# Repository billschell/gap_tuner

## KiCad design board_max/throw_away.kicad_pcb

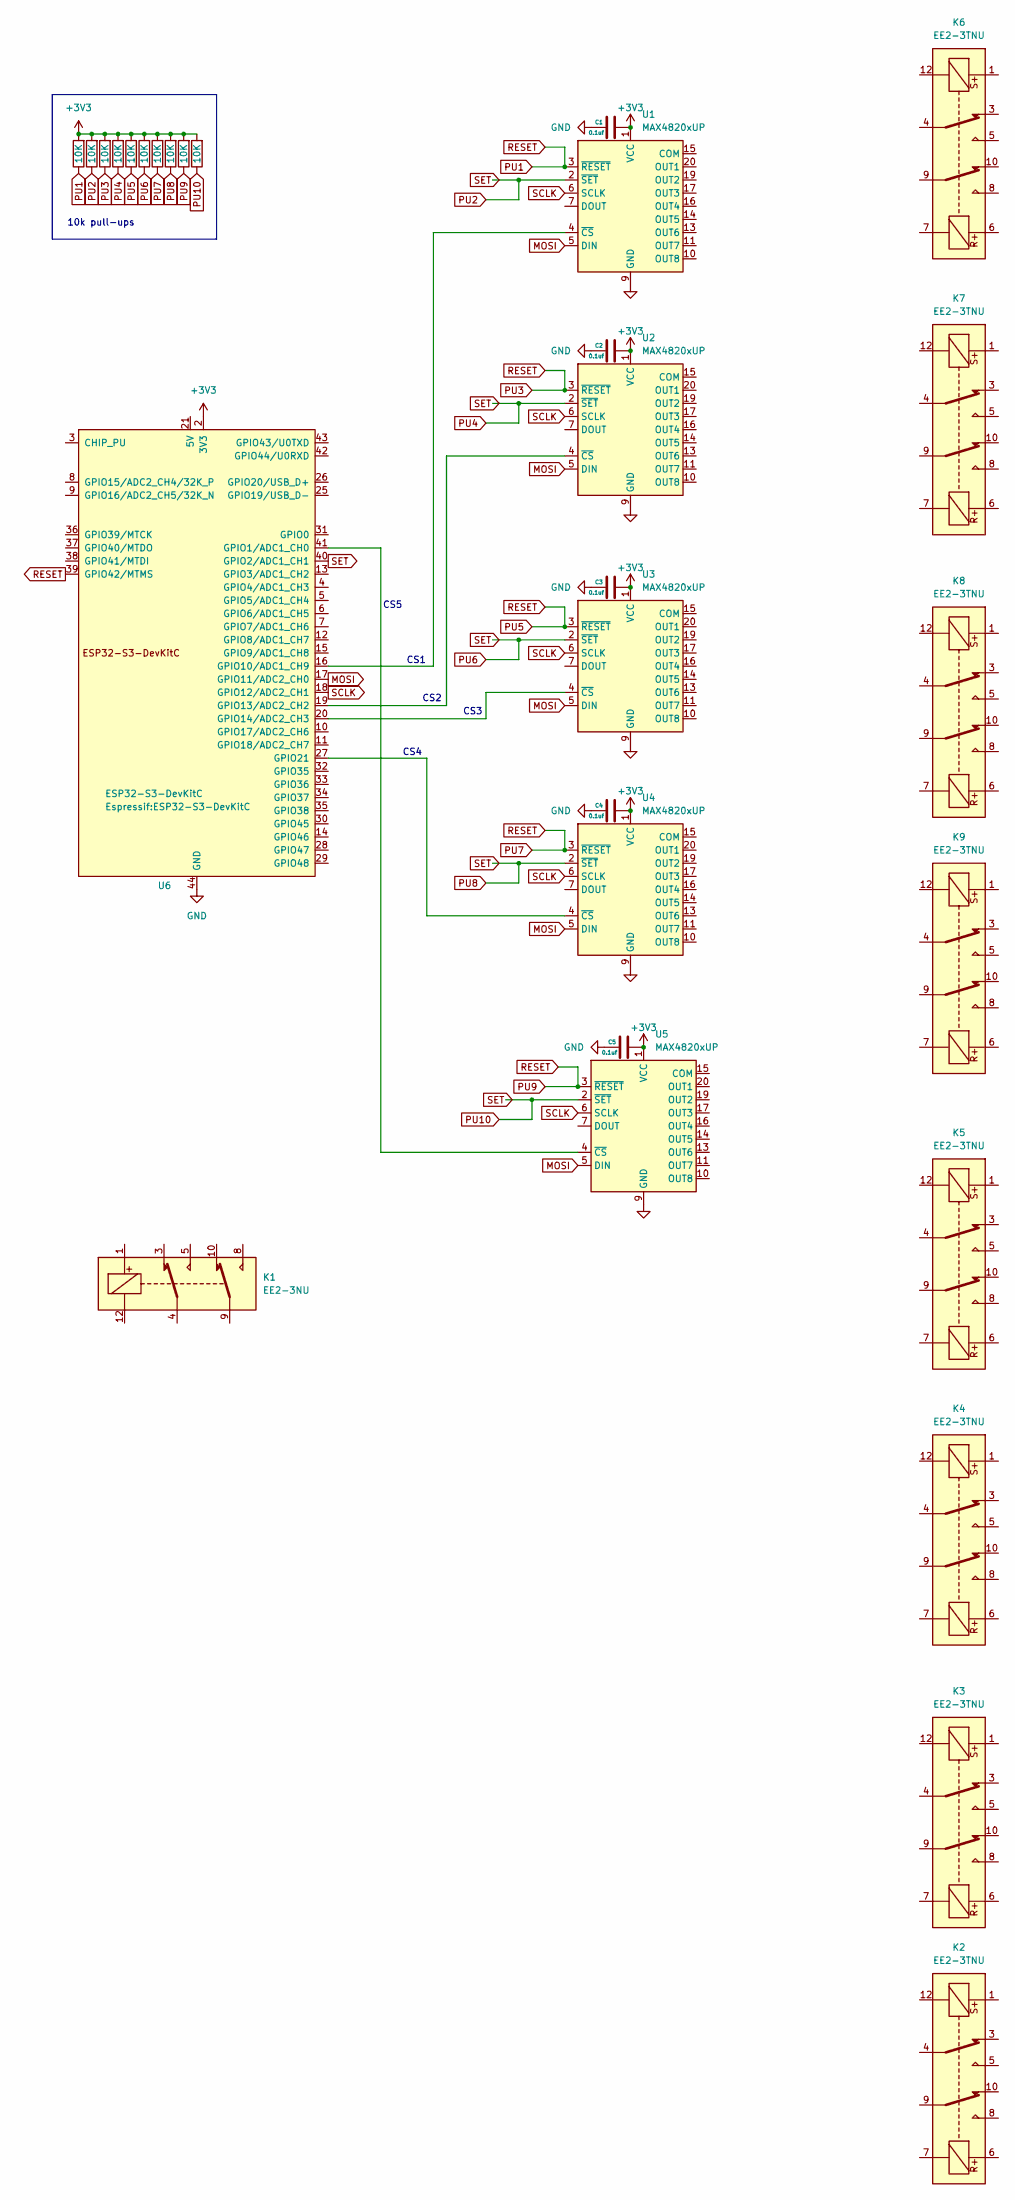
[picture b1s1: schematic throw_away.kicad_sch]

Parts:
C1, C2, C3, C4, C5: 0.1uf; C_0805_2012Metric_Pad1.18x1.45mm_HandSolder
K1: EE2-3NU; Relay_DPDT_Kemet_EE2_NU
K2, K3, K4, K5, K6, K7, K8, K9: EE2-3TNU; Relay_DPDT_Kemet_EE2_NU_DoubleCoil
R11, R12, R13, R14, R15, R16, R17, R18, R19, R20: 10K; R_0805_2012Metric_Pad1.20x1.40mm_HandSolder
U1, U2, U3, U4, U5: MAX4820xUP; HTSSOP-20-1EP_4.4x6.5mm_P0.65mm_EP2.85x4mm
U6: ESP32-S3-DevKitC

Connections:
+3V3: C1.2, C2.2, C3.2, C4.2, C5.2, R11.2, R12.2, R13.2, R14.2, R15.2, R16.2, R17.2, R18.2, R19.2, R20.2, U1.1 (VCC), U2.1 (VCC), U3.1 (VCC), U4.1 (VCC), U5.1 (VCC), U6.1 (3V3), U6.2 (3V3)
GND: C1.1, C2.1, C3.1, C4.1, C5.1, U1.9 (GND), U1.12 (GND), U1.18 (GND), U1.21 (GND), U2.9 (GND), U2.12 (GND), U2.18 (GND), U2.21 (GND), U3.9 (GND), U3.12 (GND), U3.18 (GND), U3.21 (GND), U4.9 (GND), U4.12 (GND), U4.18 (GND), U4.21 (GND), U5.9 (GND), U5.12 (GND), U5.18 (GND), U5.21 (GND), U6.22 (GND), U6.23 (GND), U6.24 (GND), U6.44 (GND)
MOSI: U1.5 (DIN), U2.5 (DIN), U3.5 (DIN), U4.5 (DIN), U5.5 (DIN), U6.17 (GPIO11/ADC2_CH0)
unnamed: U1.4 (~CS), U6.16 (GPIO10/ADC1_CH9)
unnamed: U2.4 (~CS), U6.19 (GPIO13/ADC2_CH2)
unnamed: U3.4 (~CS), U6.20 (GPIO14/ADC2_CH3)
unnamed: U4.4 (~CS), U6.27 (GPIO21)
unnamed: U5.4 (~CS), U6.41 (GPIO1/ADC1_CH0)
PU1: R11.1, R13.1, R15.1, R17.1, R19.1, U1.3 (~RESET), U2.3 (~RESET), U3.3 (~RESET), U4.3 (~RESET), U5.3 (~RESET), U6.39 (GPIO42/MTMS)
PU10: R12.1, R14.1, R16.1, R18.1, R20.1, U1.2 (~SET), U2.2 (~SET), U3.2 (~SET), U4.2 (~SET), U5.2 (~SET), U6.40 (GPIO2/ADC1_CH1)
SCLK: U1.6 (SCLK), U2.6 (SCLK), U3.6 (SCLK), U4.6 (SCLK), U5.6 (SCLK), U6.18 (GPIO12/ADC2_CH1)

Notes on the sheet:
CS5
CS2
CS1
10k pull-ups
CS4
CS3

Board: 2 copper layers, 30 parts (0 on the bottom side), 11 nets, no tracks yet.

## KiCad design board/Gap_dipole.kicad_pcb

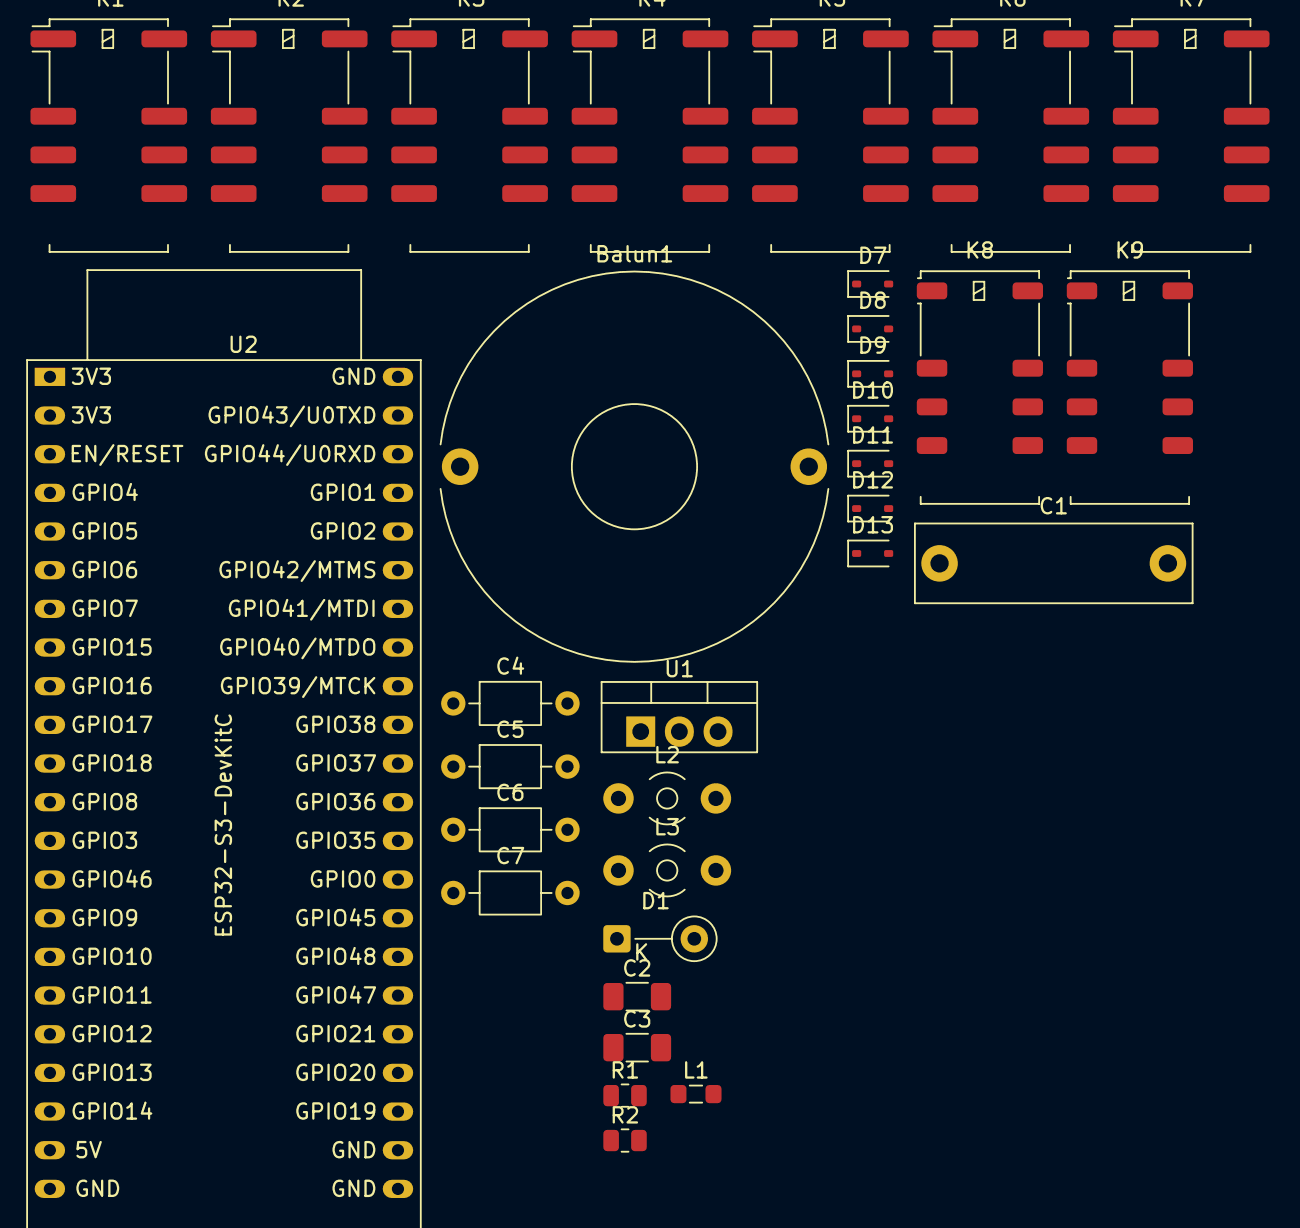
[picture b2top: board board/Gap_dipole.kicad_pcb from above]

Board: 2 copper layers, 32 parts (0 on the bottom side), 34 nets, no tracks yet.

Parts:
Balun1: toroidal core (fix connections); L_Toroid_Horizontal_D25.4mm_P22.90mm_Vishay_TJ5
C1: .47K100P (470 pF); C_Rect_L18.0mm_W5.0mm_P15.00mm_FKS3_FKP3
C2, C3: C; C_1206_3216Metric_Pad1.33x1.80mm_HandSolder
C4, C5, C6, C7: C; C_Axial_L3.8mm_D2.6mm_P7.50mm_Horizontal
D1: D; D_A-405_P5.08mm_Vertical_KathodeUp
D7, D8, D9, D10, D11, D12, D13: 1N4148WS; D_SOD-323
K1, K2, K3, K4, K5, K6, K7: EE2-3NU; Relay_DPDT_Kemet_EE2_NU
K8, K9: EE2-3SNUH; Relay_DPDT_Kemet_EE2_NUH
L1: L - bias tee; L_0805_2012Metric_Pad1.05x1.20mm_HandSolder
L2, L3: L; L_Toroid_Horizontal_D3.2mm_P6.40mm_Diameter3-5mm_Amidon-T12
R1, R2: 100Ω; R_0805_2012Metric
U1: REG; TO-220-3_Vertical
U2: ESP32-S3-DevKitC

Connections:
+3.3V: C1.2, K7.5, K7.10
GNDREF: Balun1.1 (AA), C2.2, C3.2, D7.2 (A), D8.2 (A), D9.2 (A), D10.2 (A), D11.2 (A), D12.2 (A), D13.2 (A), K1.12, K2.3, K2.10, K2.12, K3.12, K4.12, K5.12, K6.1, K7.3, K7.8, K7.12, R1.2, R2.2, U1.2 (GND)
unnamed: Balun1.2 (AB), K4.4
unnamed: K6.3, K6.10
unnamed: K5.3, K5.10
unnamed: C1.1, K1.4, K1.9, L1.1
unnamed: C4.1, K8.8
unnamed: C4.2, K8.5
unnamed: C5.1, K8.1, K8.9, L2.1
unnamed: C5.2, K8.4, K8.12, L2.2
unnamed: C6.1, K9.8
unnamed: C6.2, K9.5
unnamed: C7.1, K9.1, K9.9, L3.1
unnamed: C7.2, K9.4, K9.12, L3.2
unnamed: D1.2 (A), L1.2
unnamed: C2.1, D1.1 (K), U1.1 (VI)
unnamed: D7.1 (K), K1.1
unnamed: D8.1 (K), K2.1
unnamed: D9.1 (K), K4.1
unnamed: D10.1 (K), K3.1
unnamed: D11.1 (K), K5.1
unnamed: D12.1 (K), K7.1
unnamed: D13.1 (K), K6.12
unnamed: K1.5, K1.8, K3.4, K3.9
unnamed: K1.3, K1.10, K2.4, K2.9
unnamed: K3.3, R2.1
unnamed: K3.5, K3.8, K4.9
unnamed: K3.10, R1.1
unnamed: K4.3, K4.10
unnamed: K5.5, K6.5, K7.4
unnamed: K5.8, K6.8, K7.9
unnamed: U2.1 (3V3), U2.2 (3V3)
unnamed: U2.22 (GND), U2.23 (GND), U2.24 (GND), U2.44 (GND)
VDC: C3.1, U1.3 (VO)

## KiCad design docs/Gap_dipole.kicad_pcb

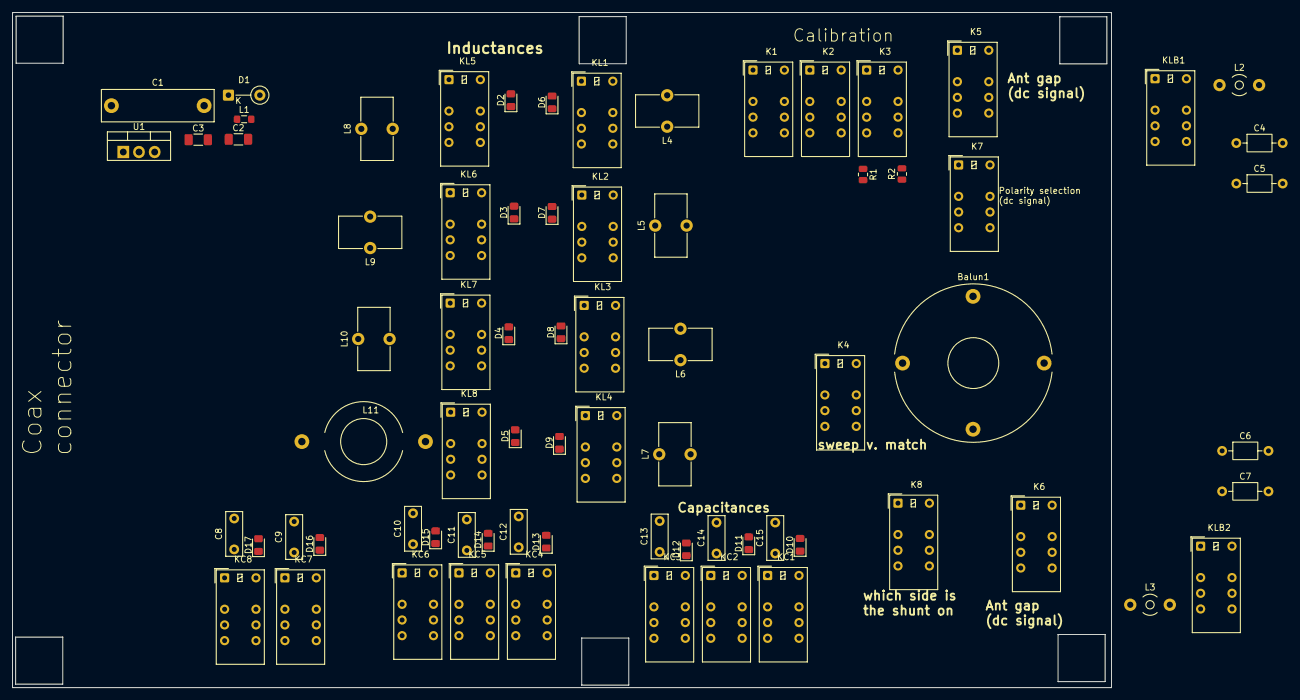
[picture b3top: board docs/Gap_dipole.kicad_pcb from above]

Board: 2 copper layers, 177.8 x 109.2 mm, 73 parts (0 on the bottom side), 21 nets, no tracks yet.

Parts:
Balun1: toroidal core (fix connections); L_Toroid_Horizontal_D25.4mm_P22.90mm_Vishay_TJ5
C1: .47K100P (470 pF); C_Rect_L18.0mm_W5.0mm_P15.00mm_FKS3_FKP3
C2, C3: C; C_1206_3216Metric_Pad1.33x1.80mm_HandSolder
C4, C5, C6, C7: C; C_Axial_L3.8mm_D2.6mm_P7.50mm_Horizontal
C8, C9, C10, C11, C12, C13, C14, C15: C; C_Disc_D7.0mm_W2.5mm_P5.00mm
D1: D; D_A-405_P5.08mm_Vertical_KathodeUp
D2, D3, D4, D5, D6, D7, D8, D9, D10, D11, D12, D13, D14, D15, D16, D17: D; D_0805_2012Metric_Pad1.15x1.40mm_HandSolder
K1, K2, K3, K5, K6, K7: Nonlatching; Relay_DPDT_Kemet_EC2_NU
K4: Nonlatching, sweep (energized) or match (unenergi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; Relay_DPDT_Kemet_EC2_NU
K8: Relay_DPDT_Latching_1coil (bipolar) sets shunt si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; Relay_DPDT_Kemet_EC2_NJ
KC1, KC2, KC3, KC4, KC5, KC6, KC7, KC8: Relay_DPDT_Latching_1coil (bipolar); Relay_DPDT_Kemet_EC2_NJ
KL1, KL2, KL3, KL4, KL5, KL6, KL7, KL8: Relay_DPDT_Latching_1coil (bipolar); Relay_DPDT_Kemet_EC2_NJ
KLB1, KLB2: Relay_DPDT_Latching_1coil (bipolar); Relay_DPDT_Kemet_EC2_NJ
L1: L - bias tee; L_0805_2012Metric_Pad1.05x1.20mm_HandSolder
L2, L3: L; L_Toroid_Horizontal_D3.2mm_P6.40mm_Diameter3-5mm_Amidon-T12
L4, L5, L6, L7, L8, L9, L10: L; L_Toroid_Vertical_L10.0mm_W5.0mm_P5.08mm
L11: L; L_Toroid_Horizontal_D12.7mm_P20.00mm_Diameter14-5mm_Amidon-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
R1, R2: 100Ω; R_0805_2012Metric
U1: REG; TO-220-3_Vertical

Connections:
+3.3V: C1.2, K7.5, K7.10
GNDREF: Balun1.1 (AA), C2.2, C3.2, K1.12, K2.5, K2.8, K2.12, K3.12, K4.12, K5.12, K6.1, K7.3, K7.8, R1.2, R2.2, U1.2 (GND)
unnamed: Balun1.2 (AB), K4.9
unnamed: Balun1.3 (SA), K6.3, K6.10
unnamed: Balun1.4 (SB), K5.3, K5.10
unnamed: C1.1, K1.4, K1.9, L1.1
unnamed: C5.1, L2.1
unnamed: C5.2, L2.2
unnamed: C7.1, L3.1
unnamed: C7.2, L3.2
unnamed: D1.2 (A), L1.2
unnamed: C2.1, D1.1 (K), U1.1 (VI)
unnamed: K1.5, K1.8, K2.4, K2.9
unnamed: K1.3, K1.10, K3.4, K3.9
unnamed: K3.5, R1.1
unnamed: K3.8, R2.1
unnamed: K3.3, K3.10, K4.4
unnamed: K4.5, K4.8
unnamed: K5.5, K6.5, K7.4
unnamed: K5.8, K6.8, K7.9
VDC: C3.1, U1.3 (VO)

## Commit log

2025-10-27 updates after Bob's review
2025-10-27 updated k3 to connect to LC when unenergized
2025-12-05 All components now on board
    Draft with all components on the board. However everything is basically a placeholder. Need actual device footprints, inc lead spacings, etc.
2025-12-13 replaced generic relays with specific parts with footprints, added diodes for relays, cleanup
2025-12-13 Squashed 'board/espressif_library/' content from commit 93d7c10
    git-subtree-dir: board/espressif_library
    git-subtree-split: 93d7c10fc5861f74ee7bd3ef871e9fa0e16bf311
2025-12-13 relay parts are right now
2025-12-13 new kicad specific .gitignore
2025-12-13 moved Library directory into board directory
2026-01-08 add kicad files for MAX4820 based board
2026-01-08 finished connecting max4820 chips to ESP32
2026-03-23 We added dual operating mode support to the GAP Tuner: Field mode (AP) is now a first-class operating mode stored in NVS flash alongside Home WiFi mode, with NetworkMgr refactored to drop its own web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
2026-03-23 ● handleWiFiStatusRequest was changed from a plain isConnected() check (always false in AP/field mode) to isConnected() || (WiFi.getMode() & WIFI_AP), so the indicator shows green whenever the ESP is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
2026-03-24 Make the N4 button be a toggle, not a pulse
2026-03-25 Added single line comments for all methods (C++ and Javascript)
2026-03-26 change reset all relays in RelayTestController.cpp, to do one relay at a time. Otherwise power consumption is very high
2026-03-27 fixed resetAll in RelayTestController.cpp to do a pulse on the L and C relays, not a "set"!
2026-03-27 made all N buttons be toggles, not pulse
2026-03-27 Hide Apply&Reset button when in field mode, as it is disabled anyway
2026-04-01 swapped LONG and SHORT buttons
